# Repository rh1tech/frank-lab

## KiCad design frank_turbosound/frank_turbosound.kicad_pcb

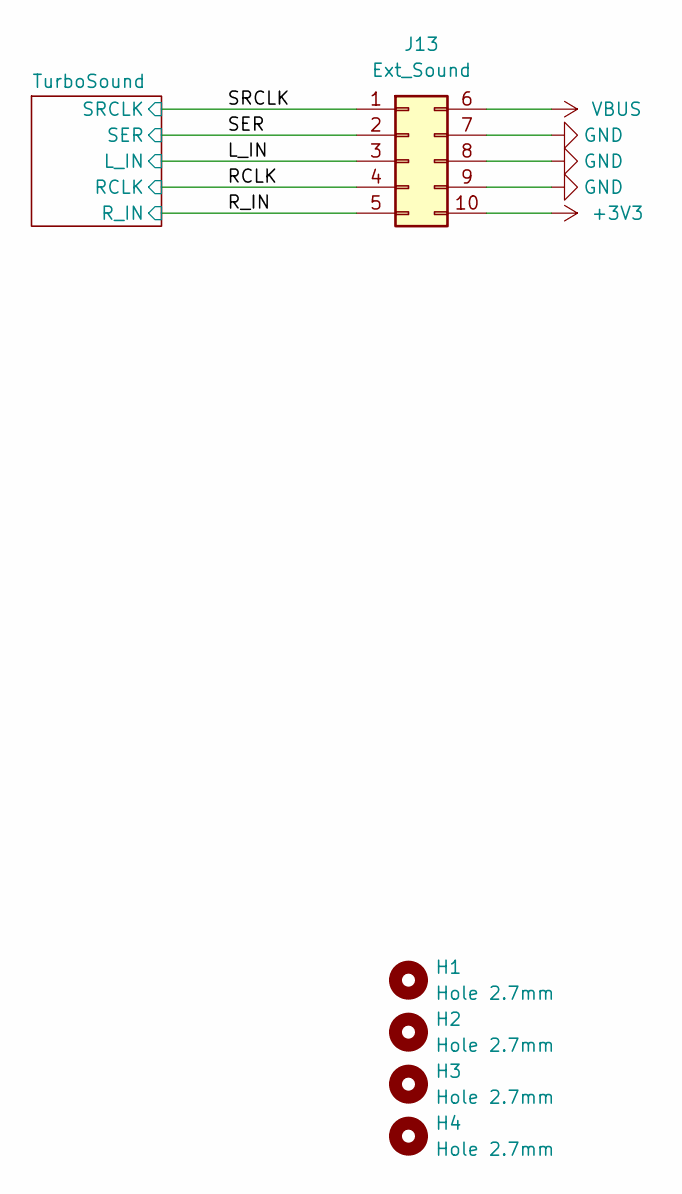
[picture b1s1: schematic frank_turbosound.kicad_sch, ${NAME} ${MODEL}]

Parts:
H1, H2, H3, H4: Hole 2.7mm; MountingHole_2.7mm
J13: Ext_Sound; IDC-Header_2x05_P2.54mm_Vertical

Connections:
+3V3: J13.10
/L_IN: J13.3; also elsewhere on the board
/RCLK: J13.4; also elsewhere on the board
/R_IN: J13.5; also elsewhere on the board
/SER: J13.2; also elsewhere on the board
/SRCLK: J13.1; also elsewhere on the board
GND: J13.7, J13.8, J13.9; also elsewhere on the board
VBUS: J13.6; also elsewhere on the board

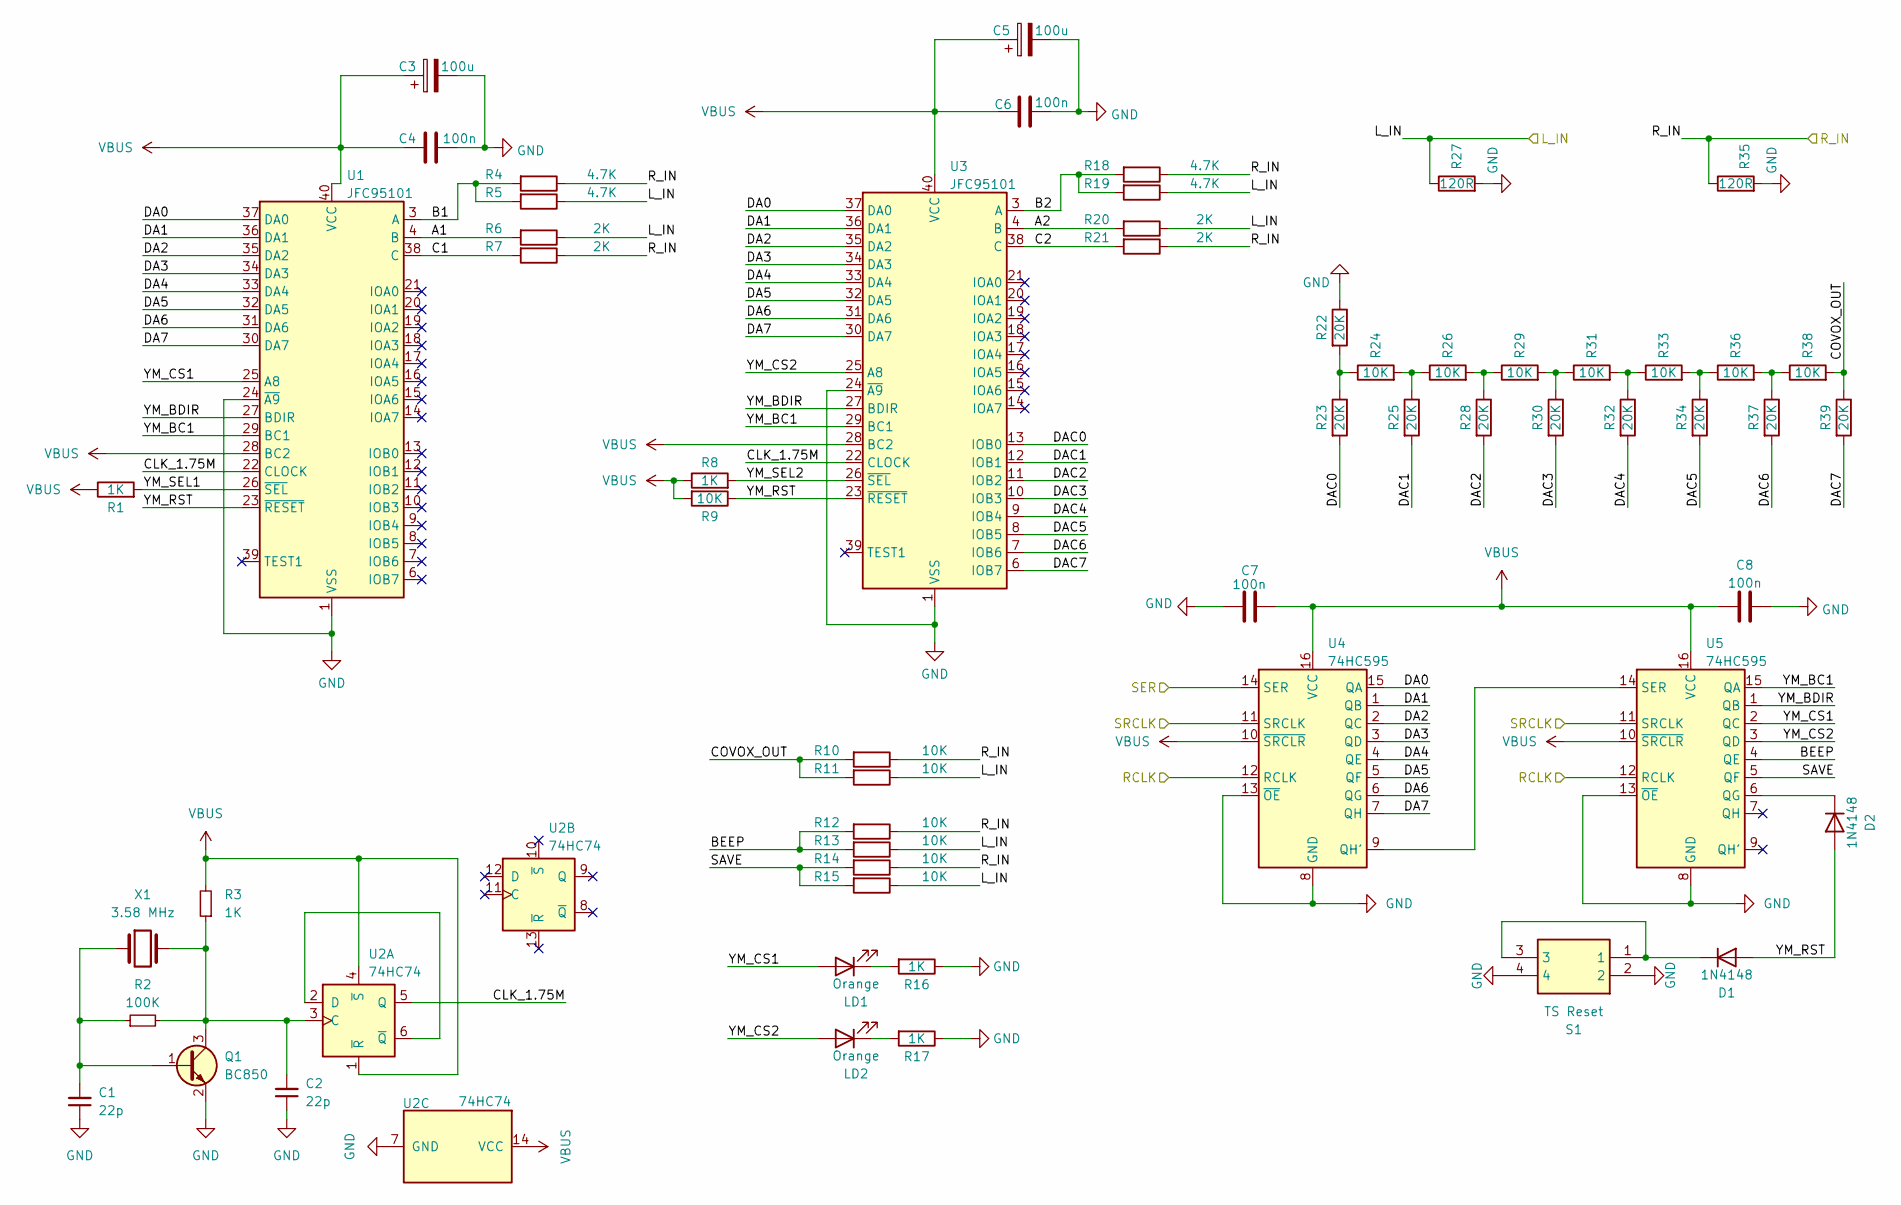
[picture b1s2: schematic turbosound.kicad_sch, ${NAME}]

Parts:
C1, C2: 22p; C_0603_1608Metric
C3, C5: 100u; CP_EIA-3528-12_Kemet-T
C4, C6, C7, C8: 100n; C_0603_1608Metric
D1, D2: 1N4148; D_SOD-323
LD1, LD2: Orange; LED_0805_2012Metric
Q1: BC850; SOT-23
R1, R3, R8, R16, R17: 1K; R_0603_1608Metric
R2: 100K; R_0603_1608Metric
R4, R5, R18, R19: 4.7K; R_0603_1608Metric
R6, R7, R20, R21: 2K; R_0603_1608Metric
R9, R10, R11, R12, R13, R14, R15, R24, R26, R29, R31, R33, R36, R38: 10K; R_0603_1608Metric
R22, R23, R25, R28, R30, R32, R34, R37, R39: 20K; R_0603_1608Metric
R27, R35: 120R; R_0603_1608Metric
S1: TS Reset; KMR_2; Mouser Part Number 611-KMR221G-LFS
U1, U3: JFC95101; DIP-40_W15.24mm_Socket
U2: 74HC74; 74HCT74D
U4, U5: 74HC595; SOP-16_3.9x9.9mm_P1.27mm
X1: 3.58 MHz; Crystal_HC49-S

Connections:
/L_IN: R5.1, R6.1, R11.1, R13.1, R15.1, R19.1, R20.1, R27.1; also elsewhere on the board
/RCLK: U4.12 (RCLK), U5.12 (RCLK); also elsewhere on the board
/R_IN: R4.1, R7.1, R10.1, R12.1, R14.1, R18.1, R21.1, R35.1; also elsewhere on the board
/SER: U4.14 (SER); also elsewhere on the board
/SRCLK: U4.11 (SRCLK), U5.11 (SRCLK); also elsewhere on the board
/TurboSound/A1: R6.2, U1.4 (B)
/TurboSound/A2: R20.2, U3.4 (B)
/TurboSound/B1: R4.2, R5.2, U1.3 (A)
/TurboSound/B2: R18.2, R19.2, U3.3 (A)
/TurboSound/BEEP: R12.2, R13.2, U5.4 (QE)
/TurboSound/C1: R7.2, U1.38 (C)
/TurboSound/C2: R21.2, U3.38 (C)
/TurboSound/CLK_1.75M: U1.22 (CLOCK), U2.5 (Q), U3.22 (CLOCK)
/TurboSound/COVOX_OUT: R10.2, R11.2, R38.2, R39.1
/TurboSound/DA0: U1.37 (DA0), U3.37 (DA0), U4.15 (QA)
/TurboSound/DA1: U1.36 (DA1), U3.36 (DA1), U4.1 (QB)
/TurboSound/DA2: U1.35 (DA2), U3.35 (DA2), U4.2 (QC)
/TurboSound/DA3: U1.34 (DA3), U3.34 (DA3), U4.3 (QD)
/TurboSound/DA4: U1.33 (DA4), U3.33 (DA4), U4.4 (QE)
/TurboSound/DA5: U1.32 (DA5), U3.32 (DA5), U4.5 (QF)
/TurboSound/DA6: U1.31 (DA6), U3.31 (DA6), U4.6 (QG)
/TurboSound/DA7: U1.30 (DA7), U3.30 (DA7), U4.7 (QH)
/TurboSound/DAC0: R23.2, U3.13 (IOB0)
/TurboSound/DAC1: R25.2, U3.12 (IOB1)
/TurboSound/DAC2: R28.2, U3.11 (IOB2)
/TurboSound/DAC3: R30.2, U3.10 (IOB3)
/TurboSound/DAC4: R32.2, U3.9 (IOB4)
/TurboSound/DAC5: R34.2, U3.8 (IOB5)
/TurboSound/DAC6: R37.2, U3.7 (IOB6)
/TurboSound/DAC7: R39.2, U3.6 (IOB7)
/TurboSound/SAVE: R14.2, R15.2, U5.5 (QF)
/TurboSound/YM_BC1: U1.29 (BC1), U3.29 (BC1), U5.15 (QA)
/TurboSound/YM_BDIR: U1.27 (BDIR), U3.27 (BDIR), U5.1 (QB)
/TurboSound/YM_CS1: LD1.2 (A), U1.25 (A8), U5.2 (QC)
/TurboSound/YM_CS2: LD2.2 (A), U3.25 (A8), U5.3 (QD)
/TurboSound/YM_RST: D1.2 (A), D2.2 (A), R9.1, U1.23 (~RESET), U3.23 (~RESET)
/TurboSound/YM_SEL1: R1.2, U1.26 (~SEL)
/TurboSound/YM_SEL2: R8.2, U3.26 (~SEL)
GND: C1.1, C2.1, C3.2, C4.2, C5.2, C6.2, C7.2, C8.2, Q1.2 (E), R16.1, R17.1, R22.1, R27.2, R35.2, S1.2, S1.4, U1.1 (VSS), U1.24 (~A9), U2.7 (GND), U3.1 (VSS), U3.24 (~A9), U4.8 (GND), U4.13 (~OE), U5.8 (GND), U5.13 (~OE); also elsewhere on the board
unnamed: D1.1 (K), S1.1, S1.3
unnamed: D2.1 (K), U5.6 (QG)
unnamed: LD1.1 (K), R16.2
unnamed: LD2.1 (K), R17.2
unnamed: C1.2, Q1.1 (B), R2.1, X1.1
unnamed: C2.2, Q1.3 (C), R2.2, R3.1, U2.3 (C), X1.2
unnamed: R22.2, R23.1, R24.1
unnamed: R24.2, R25.1, R26.1
unnamed: R26.2, R28.1, R29.1
unnamed: R29.2, R30.1, R31.1
unnamed: R31.2, R32.1, R33.1
unnamed: R33.2, R34.1, R36.1
unnamed: R36.2, R37.1, R38.1
unnamed: U2.2 (D), U2.6 (~Q)
unnamed: U4.9 (QH'), U5.14 (SER)
VBUS: C3.1, C4.1, C5.1, C6.1, C7.1, C8.1, R1.1, R3.2, R8.1, R9.2, U1.28 (BC2), U1.40 (VCC), U2.1 (~R), U2.4 (~S), U2.14 (VCC), U3.28 (BC2), U3.40 (VCC), U4.10 (~SRCLR), U4.16 (VCC), U5.10 (~SRCLR), U5.16 (VCC); also elsewhere on the board

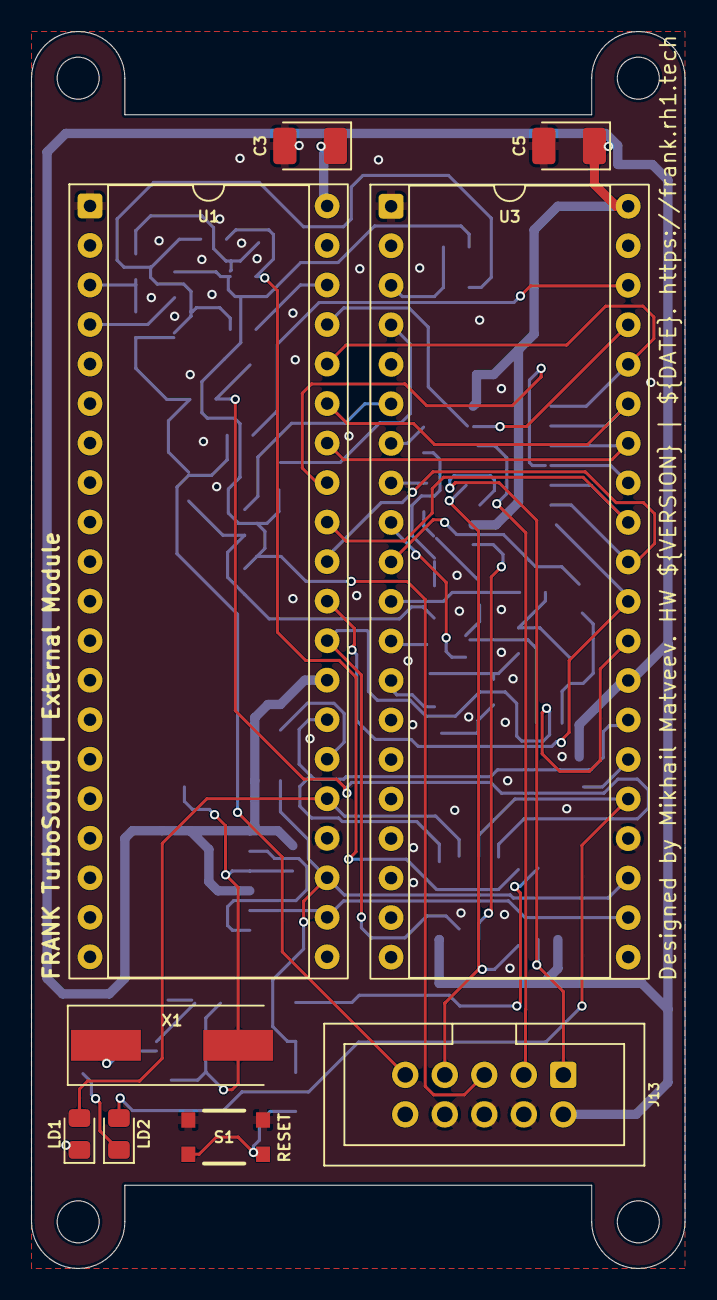
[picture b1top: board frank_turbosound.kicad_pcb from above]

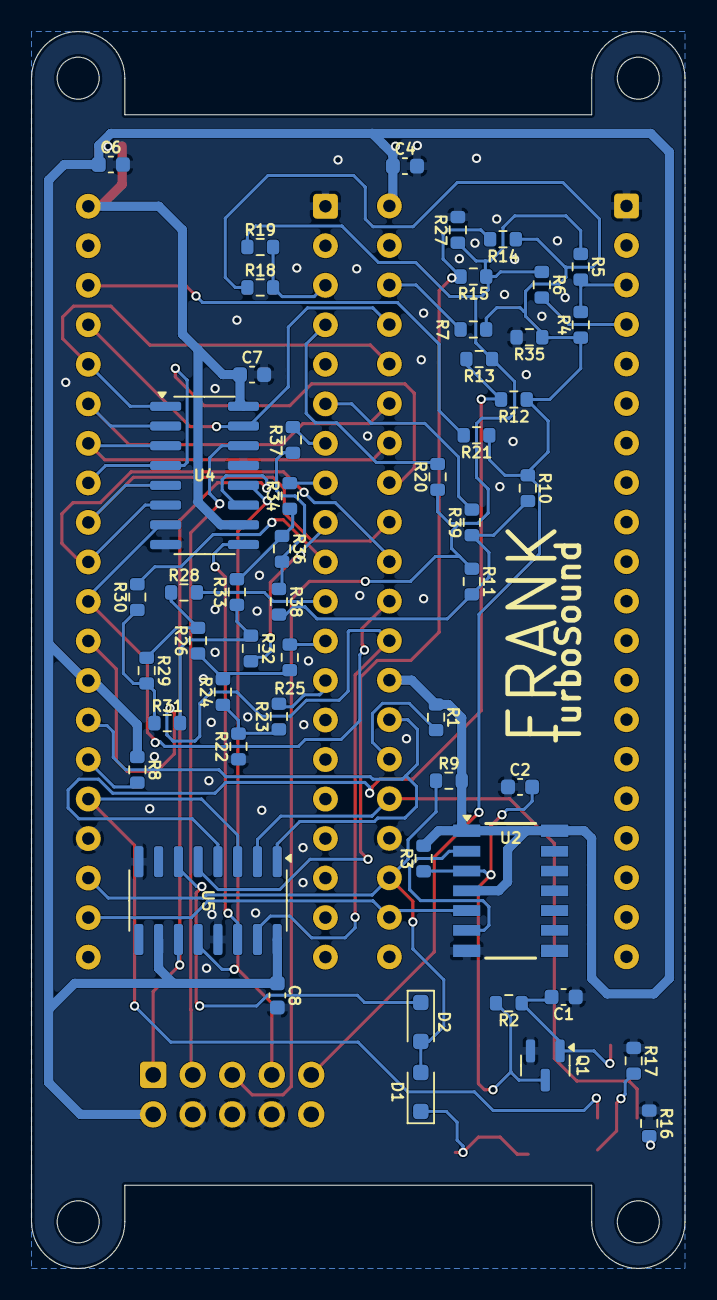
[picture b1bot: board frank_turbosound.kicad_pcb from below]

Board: 2 copper layers, 42.0 x 79.5 mm, 64 parts (51 on the bottom side), 55 nets.

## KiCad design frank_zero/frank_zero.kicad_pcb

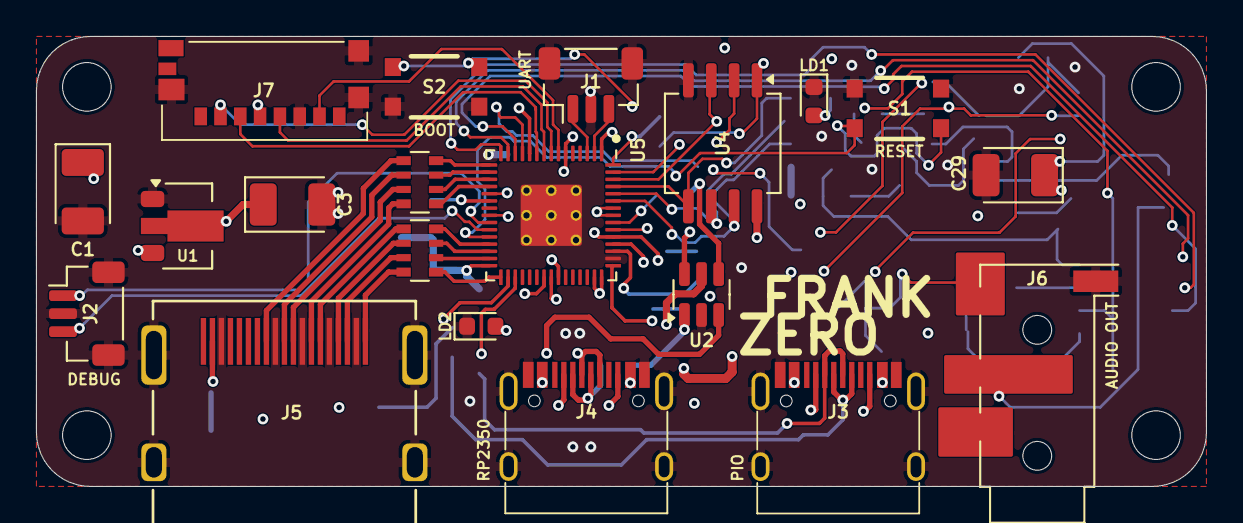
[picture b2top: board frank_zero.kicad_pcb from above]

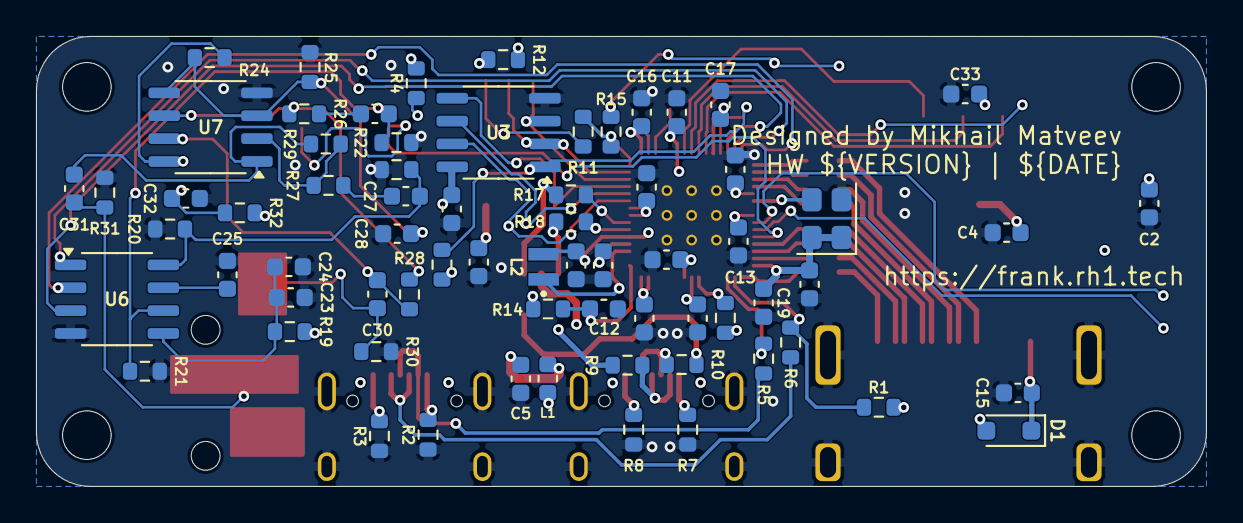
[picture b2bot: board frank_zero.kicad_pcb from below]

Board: 4 copper layers, 65.0 x 25.0 mm, 93 parts (69 on the bottom side), 79 nets.

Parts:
C1, C3: 22u; CP_Tantalum_3528-12
C2, C4, C5, C6, C7, C8, C11, C14, C15, C16, C17, C18, C19, C20, C21, C22, C24, C32, C33: 100n; C_0603_1608Metric
C9, C10, C12, C13: 4.7u; C_0603_1608Metric
C23, C25, C26, C27, C28, C30, C31: 10u; C_0603_1608Metric
C29: 10u; CP_Tantalum_3528-12
D1: 1N5819WS; D_SOD-323
H1, H2, H3, H4: Hole 2.7mm; MountingHole_2.7mm
J1: UART; JST_SH_1x03_P1.00mm_Vertical
J2: DEBUG; JST_SH_1x03_P1.00mm_Vertical
J3, J4: USB4215-03-A; USB_C_Receptacle
J5: DC3RX19JA2; HDMI_Female
J6: PJ-320D; AudioJack_3.5mm_PJ320D_AudioOut
J7: 0475710001; MicroSD_SMD_Short
L1: 330R; L_0603_1608Metric
L2: 3.3u; L_pol_2016
LD1: Green; LED_0603_1608Metric
LD2: Blue; LED_0603_1608Metric
R1: 1.5K; R_0603_1608Metric
R2, R3, R7, R8: 5.1K; R_0603_1608Metric
R4, R15, R16: 1K; R_0603_1608Metric
R5, R6, R9, R10: 22R; R_0603_1608Metric
R11: 0R; R_0603_1608Metric
R12, R13, R22, R23, R24, R25, R26, R27: 10K; R_0603_1608Metric
R14: 33R; R_0603_1608Metric
R17, R18: 27R; R_0603_1608Metric
R19, R32: 100R; R_0603_1608Metric
R20, R21: 470R; R_0603_1608Metric
R28, R29: 47K; R_0603_1608Metric
R30, R31: 20K; R_0603_1608Metric
RN1, RN2: 270R; R_Array_4x0603
S1, S2: RP Reset; KMR_2
U1: AMS1117-3.3; SOT-89-3
U2: USBLC6-2SC6; SOT-23-6
U3: ESP-PSRAM32; SO-8
U4: W25Q128JVS; SOIC-8
U5: RP2350; QFN-60_RP2350A
U6: TDA1387T; SO-8
U7: LM358; SO-8
Y1: ASE-12MHz; Oscillator_SMD_4Pin_3.2x2.5mm

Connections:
+1V1: C10.1, C11.1, C13.1, C14.1, L2.1, U5.6 (DVDD), U5.23 (DVDD), U5.39 (DVDD), U5.50 (VREG_FB)
+3V3: C3.1, C4.2, C6.1, C7.1, C8.1, C9.1, C16.1, C17.1, C18.1, C19.1, C20.1, C21.1, C22.1, C33.2, J7.P4 (VDD), R1.2, R4.2, R12.1, R13.2, R14.1, U1.2 (VO), U3.8 (VCC), U4.8 (VCC), U5.1 (IOVDD), U5.11 (IOVDD), U5.20 (IOVDD), U5.30 (IOVDD), U5.38 (IOVDD), U5.44 (ADC_AVDD), U5.45 (IOVDD), U5.49 (VREG_VIN), U5.53 (USB_OTP_VDD), U5.54 (QSPI_IOVDD), Y1.1 (EN), Y1.4 (Vdd)
/Audio/AMP_OUTL: C30.2, J6.T, R30.2
/Audio/AMP_OUTR: C31.2, J6.R, R31.2
/Audio/TDA_L: C26.1, R21.2, R22.1, U6.6 (A_LEFT)
/Audio/TDA_R: C27.1, R20.1, R23.1, U6.8 (A_RIGHT)
/D+: R17.1, U2.4 (I/O2)
/D-: R18.1, U2.6 (I/O1)
/GPIO4: J7.P7 (DAT0), U5.7 (GPIO4)
/GPIO5: J7.P2 (CD/DAT3), U5.8 (GPIO5)
/GPIO6: J7.P5 (CLK), U5.9 (GPIO6)
/GPIO7: J7.P3 (CMD), U5.10 (GPIO7)
/GPIO9: U5.13 (GPIO9), U6.3 (DATA)
/GPIO10: U5.14 (GPIO10), U6.1 (SCLK)
/GPIO11: U5.15 (GPIO11), U6.2 (LRCK)
/GPIO12: RN1.4 (R4.1), U5.16 (GPIO12)
/GPIO13: RN1.3 (R3.1), U5.17 (GPIO13)
/GPIO14: RN1.2 (R2.1), U5.18 (GPIO14)
/GPIO15: RN1.1 (R1.1), U5.19 (GPIO15)
/GPIO16: RN2.4 (R4.1), U5.27 (GPIO16)
/GPIO17: RN2.3 (R3.1), U5.28 (GPIO17)
/GPIO18: RN2.2 (R2.1), U5.29 (GPIO18)
/GPIO19: RN2.1 (R1.1), U5.31 (GPIO19)
/PIO_D+: R1.1, R6.1, U5.32 (GPIO20)
/PIO_D-: R5.1, U5.33 (GPIO21)
/Power/VBUS_IN: C5.1, J3.2 (VBUS), J3.11 (VBUS), J4.2 (VBUS), J4.11 (VBUS), L1.2
/RP2350A/FLASH_SS: R11.2, R12.2, U4.1 (~CS)
/RP2350A/GPIO0: J1.1, U5.2 (GPIO0)
/RP2350A/GPIO1: J1.3, U5.3 (GPIO1)
/RP2350A/GPIO8: R13.1, U3.1 (~CE), U5.12 (GPIO8)
/RP2350A/QSPI_SCLK: U3.6 (SCLK), U4.6 (CLK), U5.56 (QSPI_SCLK)
/RP2350A/QSPI_SD0: U3.5 (SI/SIO), U4.5 (DI(IO0)), U5.57 (QSPI_SD0)
/RP2350A/QSPI_SD1: U3.2 (SO/SIO), U4.2 (DO(IO1)), U5.59 (QSPI_SD1)
/RP2350A/QSPI_SD2: U3.3 (SIO2), U4.3 (IO2), U5.58 (QSPI_SD2)
/RP2350A/QSPI_SD3: U3.7 (SIO3), U4.7 (IO3), U5.55 (QSPI_SD3)
/RP2350A/QSPI_SS: R11.1, R15.1, U5.60 (QSPI_SS)
/RP2350A/SWCLK: J2.3, U5.24 (SWCLK)
/RP2350A/SWD: J2.1, U5.25 (SWD)
/RP2350A/VREG_AVDD: C12.1, R14.2, U5.46 (VREG_AVDD)
/RP2350A/VREG_LX: L2.2, U5.48 (VREG_LX)
/RP2350A/XIN: U5.21 (XIN), Y1.3 (OUT)
/RP2350A/~USB_BOOT: R15.2, S2.2, S2.4
/RUN: S1.2, S1.4, U5.26 (RUN)
GND: C1.2, C2.1, C3.2, C4.1, C5.2, C6.2, C7.2, C8.2, C9.2, C10.2, C11.2, C12.2, C13.2, C14.2, C15.2, C16.2, C17.2, C18.2, C19.2, C20.2, C21.2, C22.2, C23.2, C24.2, C25.2, C28.1, C29.2, C32.1, C33.1, J1.2, J2.2, J3.1 (GND), J3.12 (GND), J3.13 (SHIELD), J4.1 (GND), J4.12 (GND), J4.13 (SHIELD), J5.2 (G_D2), J5.5 (G_D1), J5.8 (G_D0), J5.11 (G_CLK), J5.17 (G_DDC/CEC), J5.20 (SHIELD1), J5.21 (SHIELD2), J5.22 (SHIELD3), J5.23 (SHIELD4), J6.S, J7.P6 (VSS), J7.SH (GND_1), LD1.1 (K), LD2.1 (K), R2.1, R3.1, R7.1, R8.1, R20.2, R21.1, R22.2, R23.2, R25.1, R30.1, R31.1, S1.1, S1.3, S2.1, S2.3, U1.1 (GND), U2.2 (GND), U3.4 (VSS), U4.4 (GND), U5.47 (VREG_PGND), U5.61 (GND), U6.4 (AGND), U7.4 (V-), Y1.2 (GND)
GPIO25: R16.2, U5.37 (GPIO25)
unnamed: C26.2, R26.2
unnamed: C27.2, R27.2
unnamed: C30.1, R28.1, U7.7
unnamed: C31.1, R29.1, U7.1
unnamed: C15.1, D1.1 (K), J5.18 (+5V)
unnamed: J3.4 (CC1), R2.2
unnamed: J3.10 (CC2), R3.2
unnamed: J3.5 (DN2), J3.7 (DN1), R5.2
unnamed: J3.6 (DP1), J3.8 (DP2), R6.2
unnamed: J4.4 (CC1), R7.2
unnamed: J4.10 (CC2), R8.2
unnamed: J4.5 (DN2), J4.7 (DN1), R9.2
unnamed: J4.6 (DP1), J4.8 (DP2), R10.2
unnamed: J5.12 (CLKN), RN1.5 (R4.2)
unnamed: J5.10 (CLKP), RN1.6 (R3.2)
unnamed: J5.9 (D0N), RN1.7 (R2.2)
unnamed: J5.7 (D0P), RN1.8 (R1.2)
unnamed: J5.6 (D1N), RN2.5 (R4.2)
unnamed: J5.4 (D1P), RN2.6 (R3.2)
unnamed: J5.3 (D2N), RN2.7 (R2.2)
unnamed: J5.1 (D2P), RN2.8 (R1.2)
unnamed: LD1.2 (A), R4.1
unnamed: LD2.2 (A), R16.1
unnamed: R9.1, U2.1 (I/O1)
unnamed: R10.1, U2.3 (I/O2)
unnamed: R18.2, U5.51 (USB_DM)
unnamed: R17.2, U5.52 (USB_DP)
unnamed: C25.1, U6.7 (FLT)
unnamed: C23.1, C24.1, R19.1, U6.5 (VA)
unnamed: C28.2, R24.1, R25.2, U7.3 (+), U7.5 (+)
unnamed: R27.1, R29.2, U7.2 (-)
unnamed: R26.1, R28.2, U7.6 (-)
unnamed: C29.1, C32.2, R24.2, R32.2, U7.8 (V+)
VBUS: C1.1, C2.2, D1.2 (A), L1.1, R19.2, R32.1, U1.3 (VI), U2.5 (VBUS)

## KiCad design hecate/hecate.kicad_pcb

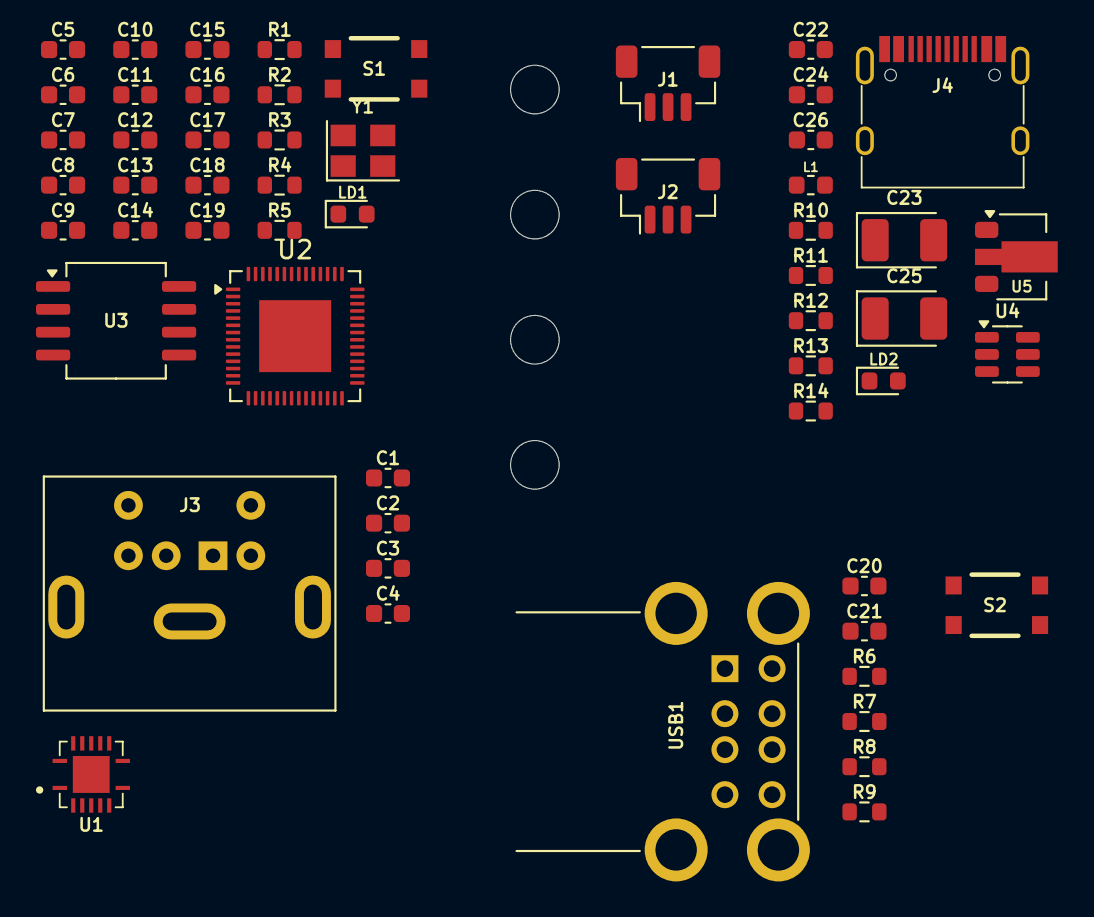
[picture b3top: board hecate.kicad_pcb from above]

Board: 2 copper layers, 60 parts (0 on the bottom side), 49 nets, no tracks yet.

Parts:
C1, C2, C3, C4, C5, C6, C8, C10, C11, C12, C13, C14, C15, C16, C19, C22, C24, C26: 100n; C_0603_1608Metric
C7, C9: 1u; C_0603_1608Metric
C17, C18: 15p; C_0603_1608Metric
C20, C21: 10u; C_0603_1608Metric
C23, C25: 22u; CP_EIA-3528-12_Kemet-T
H1, H2, H3, H4: MountingHole; MountingHole_2.7mm
J1: UART; JST_SH_BM03B-SRSS-TB_1x03-1MP_P1.00mm_Vertical
J2: DEBUG; JST_SH_BM03B-SRSS-TB_1x03-1MP_P1.00mm_Vertical
J3: MDC-036; MiniDIN_6pin_Female
J4: USB4215-03-A; USB_C_Receptacle
L1: 330R; L_0603_1608Metric
LD1: Blue; LED_0603_1608Metric
LD2: Green; LED_0603_1608Metric
R1, R2: 27R; R_0603_1608Metric
R3, R4, R5, R12: 1K; R_0603_1608Metric
R6, R7, R8, R9, R13, R14: 22R; R_0603_1608Metric
R10, R11: 5.1K; R_0603_1608Metric
S1, S2: RP Reset; KMR_2
U1: TXS0104ERGYR; RGY_S-PVQFN-N14_
U2: RP2040; QFN-56-1EP_7x7mm_P0.4mm_EP4x4mm
U3: W25Q128JVSIQ; SOIC-8
U4: USBLC6-2SC6; SOT-23-6
U5: AMS1117-3.3; SOT-89-3
USB1: USB_A_Stacked
Y1: 12 MHz; Crystal_SMD_3225-4Pin

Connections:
+3V3: C2.1, C4.1, C8.1, C9.1, C10.1, C11.1, C12.1, C13.1, C14.1, C15.1, C16.1, C19.1, C25.1, C26.2, R12.2, U1.1 (VCCA), U1.8 (OE), U2.1 (IOVDD), U2.10 (IOVDD), U2.22 (IOVDD), U2.33 (IOVDD), U2.42 (IOVDD), U2.43 (ADC_AVDD), U2.44 (VREG_IN), U2.48 (USB_VDD), U2.49 (IOVDD), U3.8 (VCC), U5.2 (VO)
/GPIO2: R6.1, U2.4 (GPIO2)
/GPIO3: R7.1, U2.5 (GPIO3)
/GPIO4: R8.1, U2.6 (GPIO4)
/GPIO5: R9.1, U2.7 (GPIO5)
/GPIO11: U1.3 (A2), U2.14 (GPIO11)
/GPIO12: U1.2 (A1), U2.15 (GPIO12)
/GPIO14: U1.5 (A4), U2.17 (GPIO14)
/GPIO15: U1.4 (A3), U2.18 (GPIO15)
/PS2/KB_CLK_5V: J3.5, U1.13 (B1)
/PS2/KB_DATA_5V: J3.1, U1.12 (B2)
/PS2/MS_CLK_5V: J3.6, U1.11 (B3)
/PS2/MS_DATA_5V: J3.2, U1.10 (B4)
/RP2040/BOOT: R4.2, S1.2, S1.4
/RP2040/D+: R1.1, U4.4 (I/O2)
/RP2040/D-: R2.1, U4.6 (I/O1)
/RP2040/GPIO0: J1.1, U2.2 (GPIO0)
/RP2040/GPIO1: J1.3, U2.3 (GPIO1)
/RP2040/GPIO25: R5.2, U2.37 (GPIO25)
/RP2040/QSPI_SCLK: U2.52 (QSPI_SCLK), U3.6 (CLK)
/RP2040/QSPI_SD0: U2.53 (QSPI_SD0), U3.5 (DI(IO0))
/RP2040/QSPI_SD1: U2.55 (QSPI_SD1), U3.2 (DO(IO1))
/RP2040/QSPI_SD2: U2.54 (QSPI_SD2), U3.3 (IO2)
/RP2040/QSPI_SD3: U2.51 (QSPI_SD3), U3.7 (IO3)
/RP2040/QSPI_SS: R4.1, U2.56 (QSPI_SS), U3.1 (~CS)
/RP2040/RUN: S2.2, S2.4, U2.26 (RUN)
/RP2040/SWCLK: J2.3, U2.24 (SWCLK)
/RP2040/SWD: J2.1, U2.25 (SWD)
/RP2040/XIN: C18.1, U2.20 (XIN), Y1.1
/RP2040/XOUT: R3.1, U2.21 (XOUT)
/USB C/VBUS_IN: C22.1, J4.2 (VBUS), J4.11 (VBUS), L1.2
GND: C1.2, C2.2, C3.2, C4.2, C5.2, C6.2, C7.2, C8.2, C9.2, C10.2, C11.2, C12.2, C13.2, C14.2, C15.2, C16.2, C17.2, C18.2, C19.2, C20.2, C21.2, C22.2, C23.2, C24.1, C25.2, C26.1, J1.2, J2.2, J3.3, J4.1 (GND), J4.12 (GND), J4.13 (SHIELD), LD1.1 (K), LD2.1 (K), R10.1, R11.1, S1.1, S1.3, S2.1, S2.3, U1.7 (GND), U1.15 (THERMAL_PAD), U2.19 (TESTEN), U2.57 (GND), U3.4 (GND), U4.2 (GND), U5.1 (GND), USB1.4 (GND1), USB1.8 (GND2), USB1.SH (Shield), Y1.2 (G), Y1.4 (G)
unnamed: C17.1, R3.2, Y1.3
unnamed: J4.4 (CC1), R10.2
unnamed: J4.10 (CC2), R11.2
unnamed: J4.5 (DN2), J4.7 (DN1), R13.2
unnamed: J4.6 (DP1), J4.8 (DP2), R14.2
unnamed: LD1.2 (A), R5.1
unnamed: LD2.2 (A), R12.1
unnamed: R13.1, U4.1 (I/O1)
unnamed: R14.1, U4.3 (I/O2)
unnamed: R2.2, U2.46 (USB_DM)
unnamed: R1.2, U2.47 (USB_DP)
unnamed: C5.1, C6.1, C7.1, U2.23 (DVDD), U2.45 (VREG_VOUT), U2.50 (DVDD)
unnamed: R6.2, USB1.3 (D1+)
unnamed: R7.2, USB1.2 (D1-)
unnamed: R8.2, USB1.7 (D2+)
unnamed: R9.2, USB1.6 (D2-)
VBUS: C1.1, C3.1, C20.1, C21.1, C23.1, C24.2, J3.4, L1.1, U1.14 (VCCB), U4.5 (VBUS), U5.3 (VI), USB1.1 (VBUS1), USB1.5 (VBUS2)

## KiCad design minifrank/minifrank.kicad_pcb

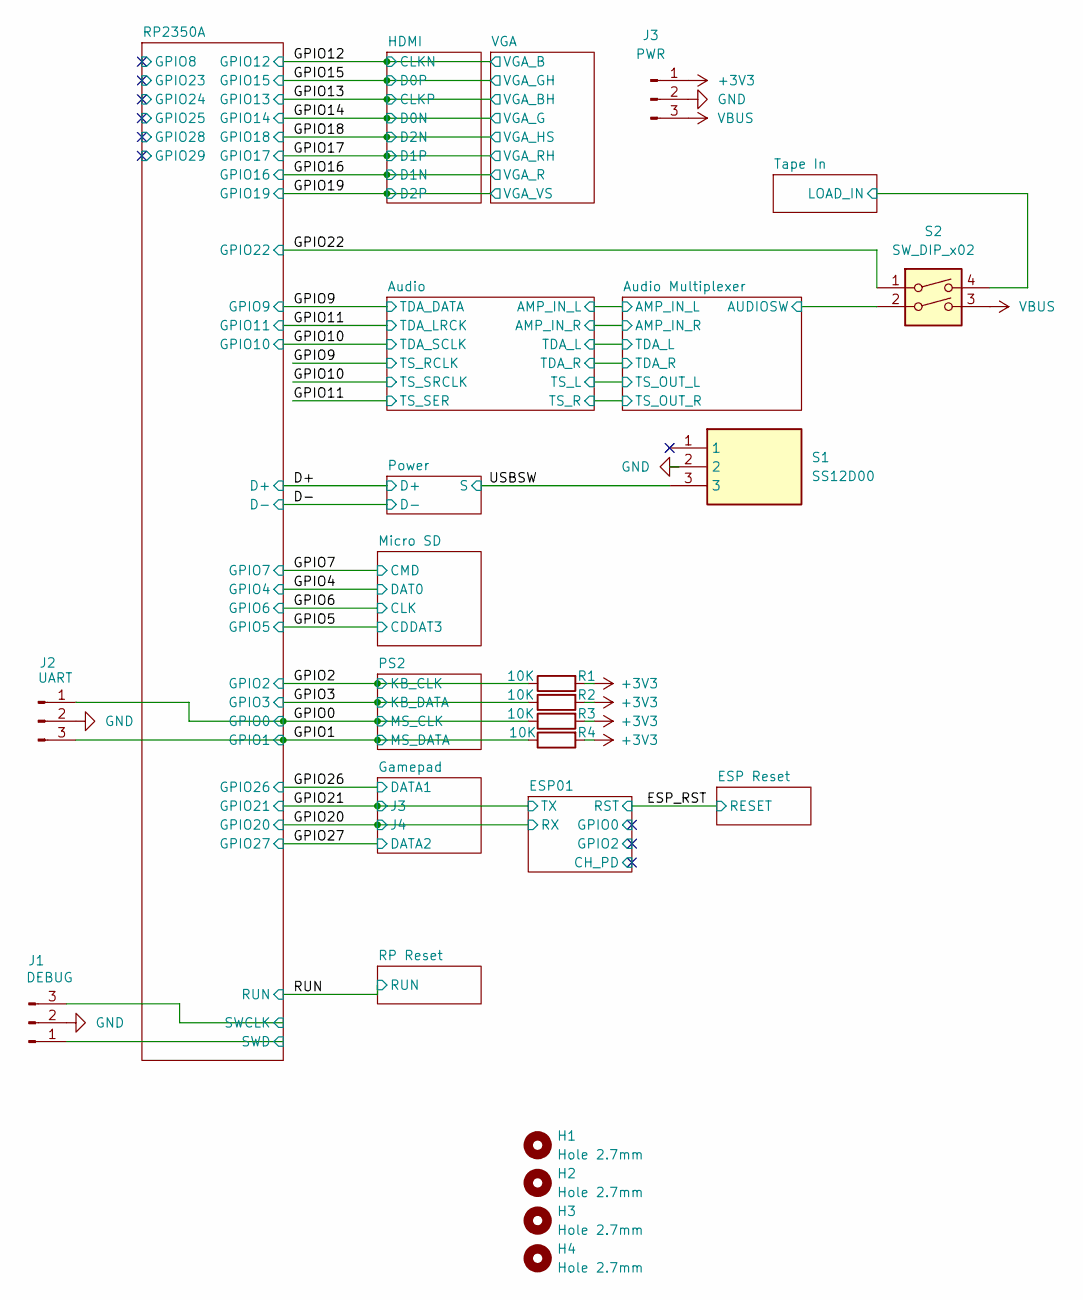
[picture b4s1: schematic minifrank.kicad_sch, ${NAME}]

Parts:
H1, H2, H3, H4: Hole 2.7mm; Mounting Hole (2.7mm)
J1: DEBUG; JST_SH_BM03B-SRSS-TB_1x03-1MP_P1.00mm_Vertical
J2: UART; JST_SH_BM03B-SRSS-TB_1x03-1MP_P1.00mm_Vertical
J3: PWR; Pin Header (1x03)
R1, R2, R3, R4: 10K; R_0603_1608Metric
S1: SS12D00; Switch_Slide_SS12D00; Mouser Part Number 611-SK12D07VG3NS
S2: SW_DIP_x02; SW_DIP_SPSTx02_Slide_9.78x7.26mm_W7.62mm_P2.54mm

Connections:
+3V3: J3.1, R1.2, R2.2, R3.2, R4.2; also elsewhere on the board
/Audio Multiplexer/AUDIOSW: S2.2; also elsewhere on the board
/GPIO0: J2.1, R3.1; also elsewhere on the board
/GPIO1: J2.3, R4.1; also elsewhere on the board
/GPIO2: R1.1; also elsewhere on the board
/GPIO3: R2.1; also elsewhere on the board
/GPIO22: S2.1; also elsewhere on the board
/RP2350A/SWCLK: J1.3; also elsewhere on the board
/RP2350A/SWD: J1.1; also elsewhere on the board
/Tape In/LOAD_IN: S2.4; also elsewhere on the board
/USBSW: S1.1, S1.3; also elsewhere on the board

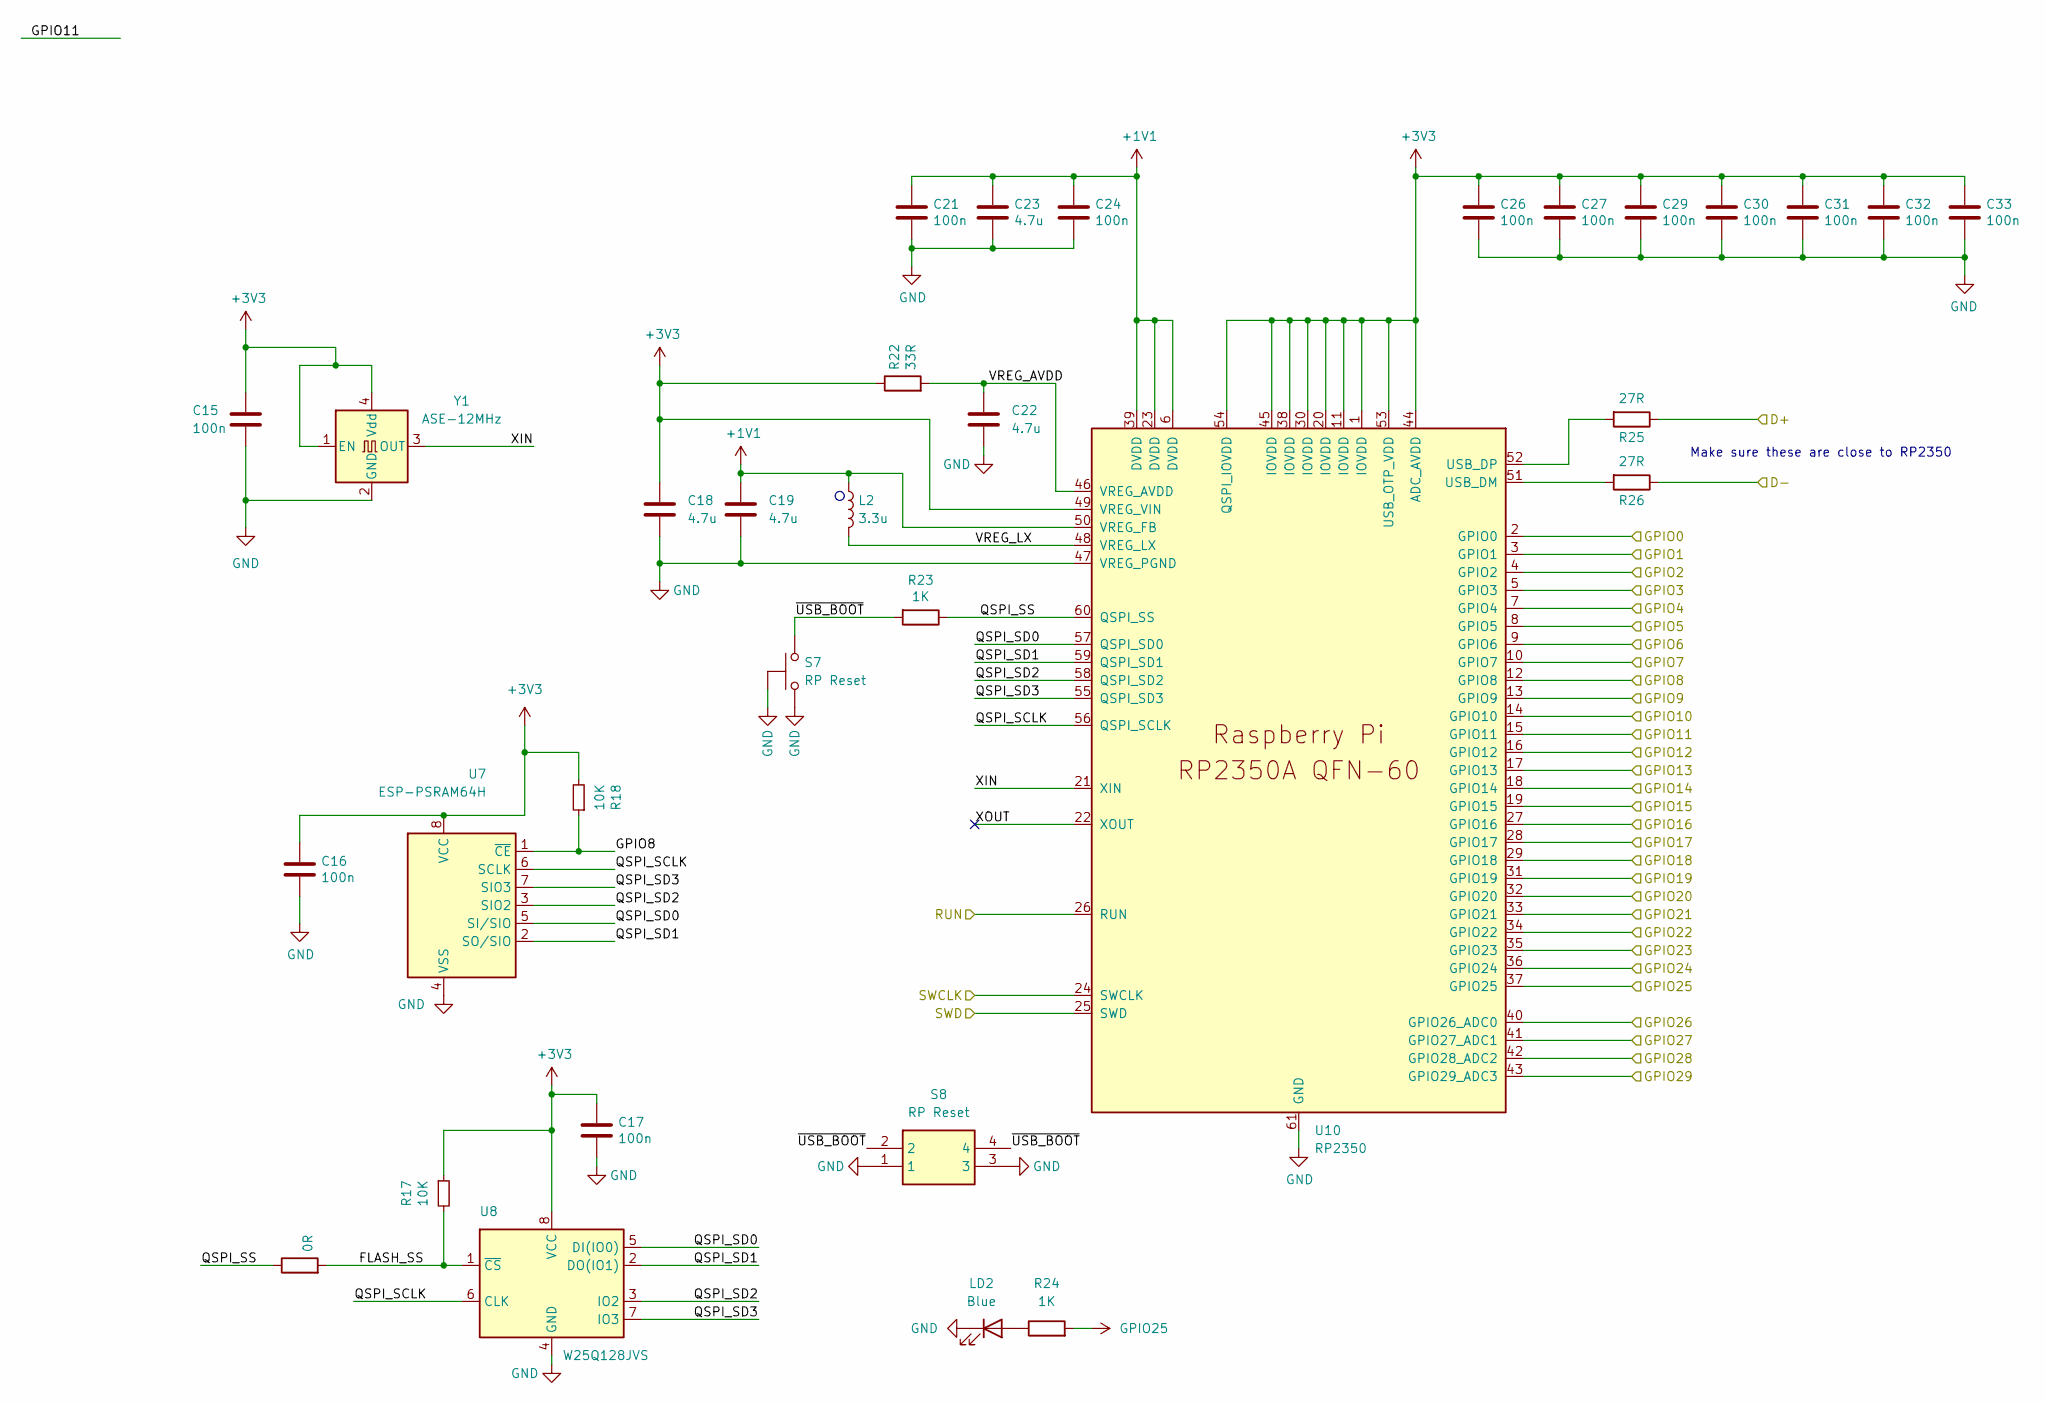
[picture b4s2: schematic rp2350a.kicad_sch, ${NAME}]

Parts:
C15, C16, C17, C21, C24, C26, C27, C29, C30, C31, C32, C33: 100n; C_0603_1608Metric
C18, C19, C22, C23: 4.7u; C_0603_1608Metric
L2: 3.3u; L_pol_2016
LD2: Blue; LED_0603_1608Metric
R16: 0R; R_0603_1608Metric
R17, R18: 10K; R_0603_1608Metric
R22: 33R; R_0603_1608Metric
R23, R24: 1K; R_0603_1608Metric
R25, R26: 27R; R_0603_1608Metric
S7: RP Reset; TS-1234VW
S8: RP Reset; KMR_2; Mouser Part Number 611-KMR221G-LFS
U7: ESP-PSRAM64H; SO-8
U8: W25Q128JVS; SOIC-8
U10: RP2350; QFN 60 (RP2350A)
Y1: ASE-12MHz; Oscillator_SMD_Abracon_ASE-4Pin_3.2x2.5mm

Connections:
+1V1: C19.1, C21.1, C23.1, C24.1, L2.1, U10.6 (DVDD), U10.23 (DVDD), U10.39 (DVDD), U10.50 (VREG_FB)
+3V3: C15.1, C16.1, C17.1, C18.1, C26.1, C27.1, C29.1, C30.1, C31.1, C32.1, C33.1, R17.1, R18.2, R22.1, U7.8 (VCC), U8.8 (VCC), U10.1 (IOVDD), U10.11 (IOVDD), U10.20 (IOVDD), U10.30 (IOVDD), U10.38 (IOVDD), U10.44 (ADC_AVDD), U10.45 (IOVDD), U10.49 (VREG_VIN), U10.53 (USB_OTP_VDD), U10.54 (QSPI_IOVDD), Y1.1 (EN), Y1.4 (Vdd); also elsewhere on the board
/D+: R25.1; also elsewhere on the board
/D-: R26.1; also elsewhere on the board
/GPIO0: U10.2 (GPIO0); also elsewhere on the board
/GPIO1: U10.3 (GPIO1); also elsewhere on the board
/GPIO2: U10.4 (GPIO2); also elsewhere on the board
/GPIO3: U10.5 (GPIO3); also elsewhere on the board
/GPIO4: U10.7 (GPIO4); also elsewhere on the board
/GPIO5: U10.8 (GPIO5); also elsewhere on the board
/GPIO6: U10.9 (GPIO6); also elsewhere on the board
/GPIO7: U10.10 (GPIO7); also elsewhere on the board
/GPIO9: U10.13 (GPIO9); also elsewhere on the board
/GPIO10: U10.14 (GPIO10); also elsewhere on the board
/GPIO11: U10.15 (GPIO11); also elsewhere on the board
/GPIO12: U10.16 (GPIO12); also elsewhere on the board
/GPIO13: U10.17 (GPIO13); also elsewhere on the board
/GPIO14: U10.18 (GPIO14); also elsewhere on the board
/GPIO15: U10.19 (GPIO15); also elsewhere on the board
/GPIO16: U10.27 (GPIO16); also elsewhere on the board
/GPIO17: U10.28 (GPIO17); also elsewhere on the board
/GPIO18: U10.29 (GPIO18); also elsewhere on the board
/GPIO19: U10.31 (GPIO19); also elsewhere on the board
/GPIO20: U10.32 (GPIO20); also elsewhere on the board
/GPIO21: U10.33 (GPIO21); also elsewhere on the board
/GPIO22: U10.34 (GPIO22); also elsewhere on the board
/GPIO26: U10.40 (GPIO26_ADC0); also elsewhere on the board
/GPIO27: U10.41 (GPIO27_ADC1); also elsewhere on the board
/RP2350A/FLASH_SS: R16.2, R17.2, U8.1 (~CS)
/RP2350A/GPIO8: R18.1, U7.1 (~CE), U10.12 (GPIO8)
/RP2350A/GPIO23: U10.35 (GPIO23)
/RP2350A/GPIO24: U10.36 (GPIO24)
/RP2350A/GPIO28: U10.42 (GPIO28_ADC2)
/RP2350A/GPIO29: U10.43 (GPIO29_ADC3)
/RP2350A/QSPI_SCLK: U7.6 (SCLK), U8.6 (CLK), U10.56 (QSPI_SCLK)
/RP2350A/QSPI_SD0: U7.5 (SI/SIO), U8.5 (DI(IO0)), U10.57 (QSPI_SD0)
/RP2350A/QSPI_SD1: U7.2 (SO/SIO), U8.2 (DO(IO1)), U10.59 (QSPI_SD1)
/RP2350A/QSPI_SD2: U7.3 (SIO2), U8.3 (IO2), U10.58 (QSPI_SD2)
/RP2350A/QSPI_SD3: U7.7 (SIO3), U8.7 (IO3), U10.55 (QSPI_SD3)
/RP2350A/QSPI_SS: R16.1, R23.1, U10.60 (QSPI_SS)
/RP2350A/SWCLK: U10.24 (SWCLK); also elsewhere on the board
/RP2350A/SWD: U10.25 (SWD); also elsewhere on the board
/RP2350A/VREG_AVDD: C22.1, R22.2, U10.46 (VREG_AVDD)
/RP2350A/VREG_LX: L2.2, U10.48 (VREG_LX)
/RP2350A/XIN: U10.21 (XIN), Y1.3 (OUT)
/RP2350A/XOUT: U10.22 (XOUT)
/RP2350A/~USB_BOOT: R23.2, S7.2, S8.2, S8.4
/RUN: U10.26 (RUN); also elsewhere on the board
GPIO25: R24.2, U10.37 (GPIO25)
unnamed: LD2.2 (A), R24.1
unnamed: R26.2, U10.51 (USB_DM)
unnamed: R25.2, U10.52 (USB_DP)

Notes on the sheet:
Make sure these are close to RP2350

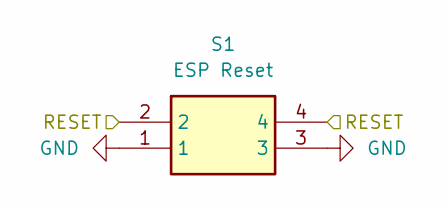
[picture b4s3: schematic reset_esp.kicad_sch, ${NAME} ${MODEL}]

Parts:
S1: ESP Reset; KMR_2; Mouser Part Number 611-KMR221G-LFS

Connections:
/USBSW: S1.1, S1.3; also elsewhere on the board

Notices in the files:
minifrank/minifrank.kicad_pcb:
© 2026 Mikhail Matveev
